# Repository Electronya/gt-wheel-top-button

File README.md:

# gt-wheel-top-button
DIY GT Wheel Top Button

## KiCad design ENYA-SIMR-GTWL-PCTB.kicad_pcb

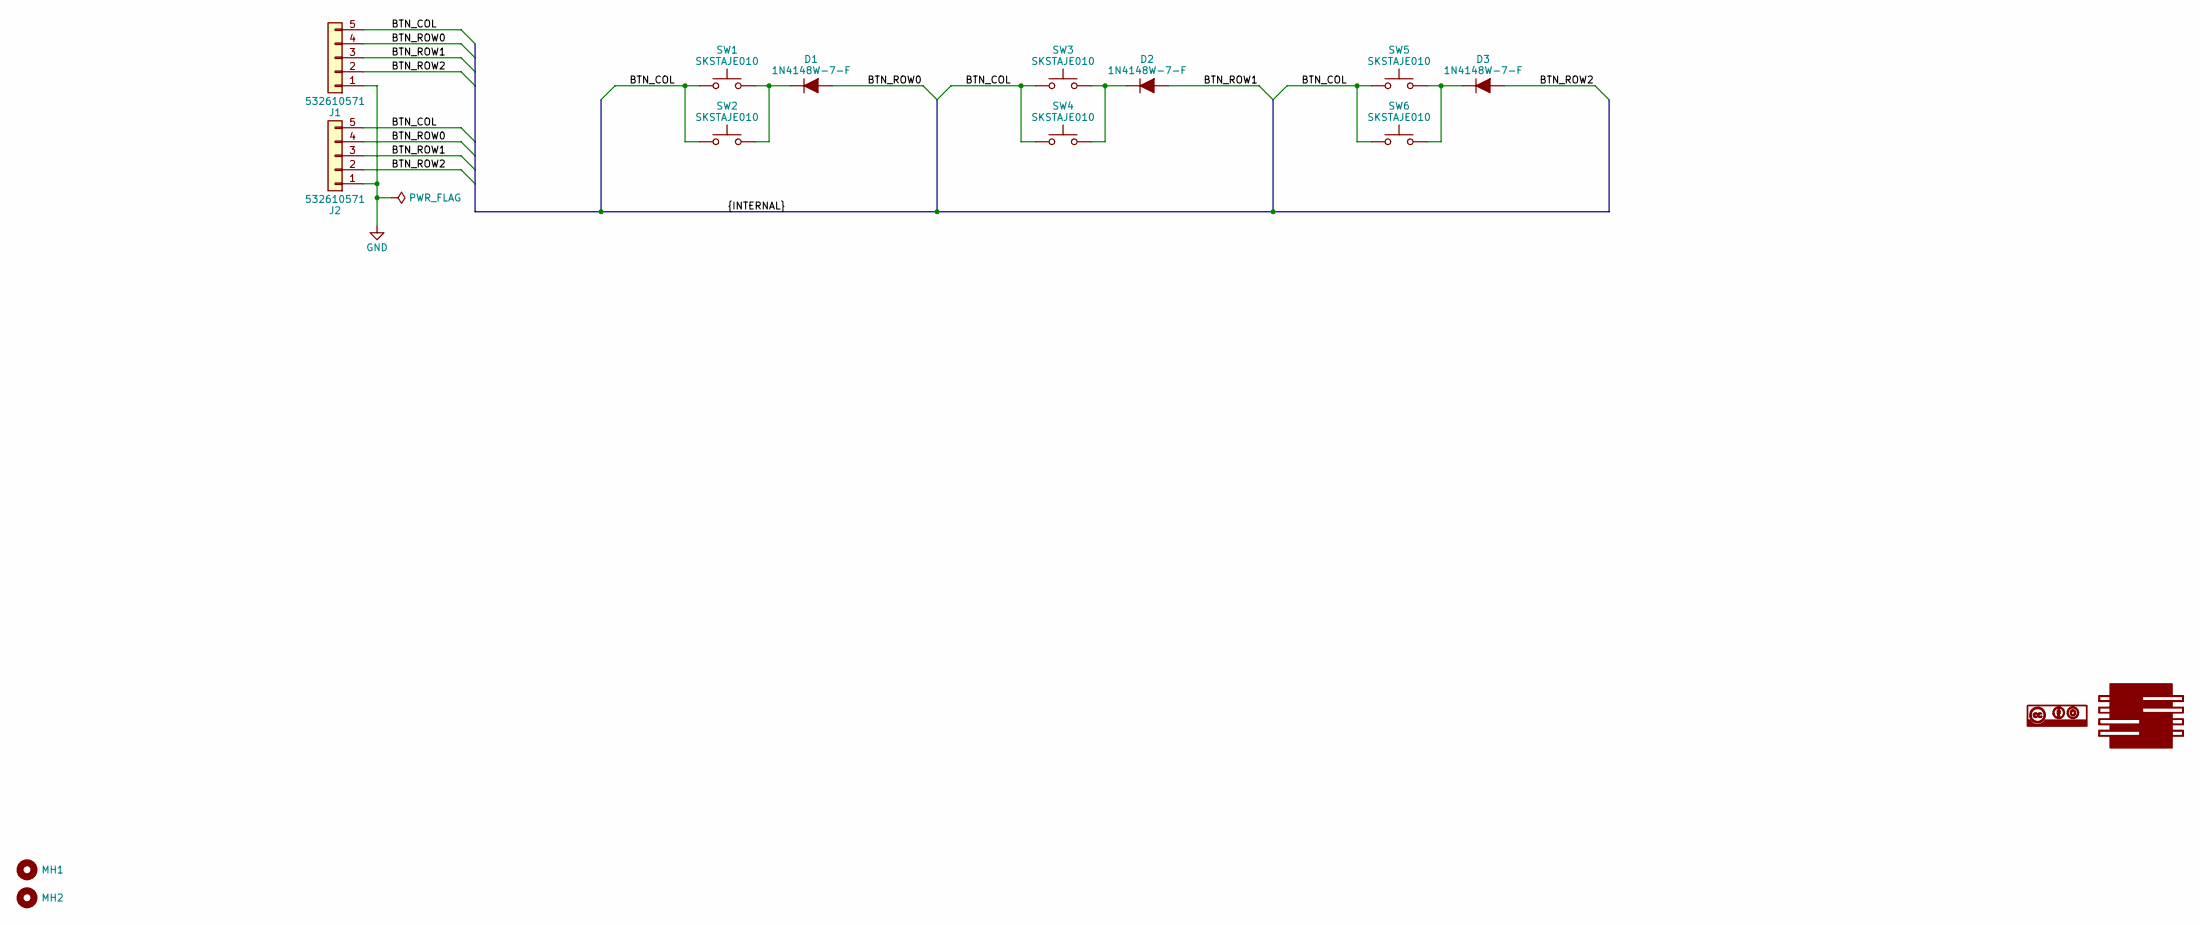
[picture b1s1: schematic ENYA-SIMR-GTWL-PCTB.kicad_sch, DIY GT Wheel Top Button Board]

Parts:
D1, D2, D3: 1N4148W-7-F; D_SOD-123; Manufacturer Part Number 1N4148W-7-F; Digi-Key Part Number 1N4148W-FDICT-ND
G1: Electronya_Logo; Electronya_Logo_10MM
G2: CC-BY-SA_Logo; CC-BY-SA_8MM
J1, J2: PICO_BLADE_1x5_MALE_RA_SMD; PICO_BLADE_53261_1x5_SMD_RA_1.25MM; Manufacturer Part Number 532610571; Digi-Key Part Number WM7623CT-ND
MH1, MH2: MH-NPLTD-M3; MountingHole_3.2mm_M3_DIN965
SW1, SW2, SW3, SW4, SW5, SW6: SKSTAJE010; SKSTAJE_Alps_SPST; Manufacturer Part Number SKSTAJE010; Mouser Part Number 688-SKSTAJE010

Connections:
/BTN_COL: J1.5, J2.5, SW1.1, SW2.1, SW3.1, SW4.1, SW5.1, SW6.1
/BTN_ROW0: D1.2 (A), J1.4, J2.4
/BTN_ROW1: D2.2 (A), J1.3, J2.3
/BTN_ROW2: D3.2 (A), J1.2, J2.2
GND: J1.1, J2.1
unnamed: D1.1 (K), SW1.2, SW2.2
unnamed: D2.1 (K), SW3.2, SW4.2
unnamed: D3.1 (K), SW5.2, SW6.2

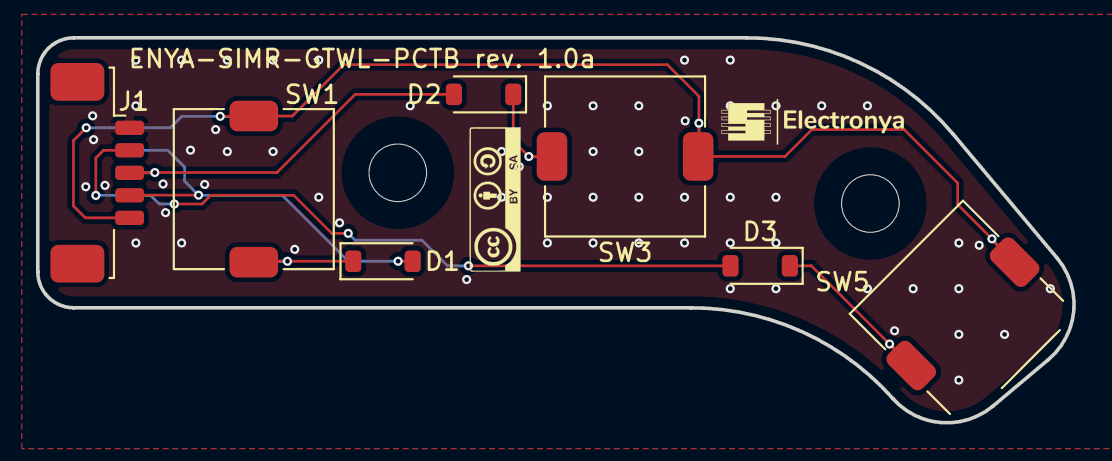
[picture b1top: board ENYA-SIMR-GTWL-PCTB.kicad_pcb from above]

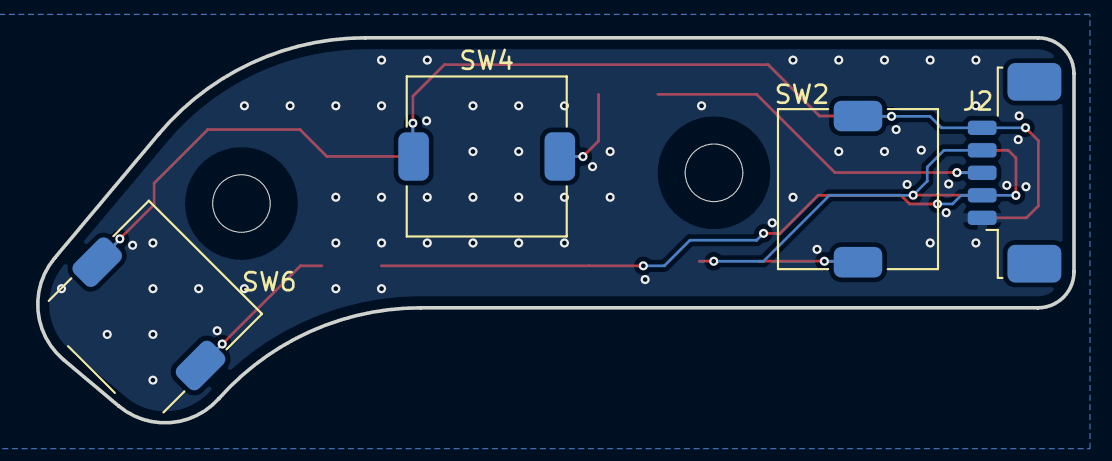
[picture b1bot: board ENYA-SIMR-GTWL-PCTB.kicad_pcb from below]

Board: 2 copper layers, 57.6 x 21.4 mm, 15 parts (4 on the bottom side), 8 nets.

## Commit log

2023-06-30 ready to tag
2023-07-01 correction button matrix diode polarity

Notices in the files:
parts and their libraries:
CC-BY-SA, creative common
